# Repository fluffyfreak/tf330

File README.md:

# tf330

TF330 source files. 

Published under GPL v2. 

TF330 is distributed with absolutely no warranty. If you make a mistake you could blow up your CD32. I take no responsibility for this. 

The TF330 is an 030 accelerator fixed at 50Mhz with 64Mb of SDRAM (128Mb possible), WIFI support (via ESP8266) and is intended to work with CF cards or IDE2SD card type devices. The IDE interface does not work with long cables. It is intended to be CHEAP Because thats pretty much all Amiga users care about. 

**Before you start building :- You can buy these from Supaduper & AlenPPC (AmiBay) completely built for less than it will cost you to buy the parts and the time it will take you if you bill your time at minimum wage.**

If you have poor soldering skills and feel the need to mock me for not using through hole technology please dont bother. I've heard it all before and I will just laugh at you. Through hole sucks. 

Also do not ask me to reroute the board to a different DRC so you can use your local boardhouse. I dont feel like spending 100 hours of my time to save you $10. The DRC on this board is 7-7-7 and any boardhouse that doesnt totally suck can do this. Also it 4 layer and dont ask if i can be made 2 layer. The answer is no. 

If you need help with this the best place to get it is the exxos forum https://www.exxoshost.co.uk/forum/ 

Please do not message me directly. Start a thread. 

I do my best to help people who ask polite questions in public but if you make your inadequecies my problem then you are on your own. 

I dont care if you think my HDL is not pristine either. It works perfecly fine for what its intended to be. I lothe the wordy VHDL language.. it breaks the most basic principle of coding .. .DONT REPEAT YOURSELF. There is a full regression test suite in my development repo that I have chosen not to share.

The SDRAM Controller is derived from my Archie core and the clock controller code is designed to simulate a PLL with adjustable phase. 

This is not an exercise in German over engineering. Its properly engineered to do an exact task and nothing more. Its a simple repeatable board that works and there are about 500 of them built and working reliably.

I dont like forks because i dont like options. Options mean more testing and more testing = time. So if you fork you are on your own but if you fork and dont give credit I will make it my mission in life to punish you. I will summon the ancient retro spirits of evil like Jack Tramiel and have them haunt you for all time. You have been warned. 

I know this seems a bit hostile but really its just from hard experience of Amiga people. I give this out for free but there are people out there who will take the piss and try to rip off amiga users with clones baring their own name, others will get one of these off ebay for £15 and expect me to invest 100s of hours in helping them get it going. Yet others will try to be smart arses and tell me i've done X, Y or Z wrong and this will never work. If for any reason you decide this board does not measure up to whatever standard YOU think it should be... take a hike. I dont care. 

That said you are free to sell this on your webshop provided you give credit and do not vastly overprice it. However CE marking is your own issue not mine. 

On the other hand if you have an actual firmware bugfix send me a pull request with testing evidence. It will be appreciated greatly. 

For crashes please check that the crash doesnt happen in WinUAE for a CD32 with A1200 IDE and 64MB ZIII Ram before making a bug report. Most of the crashes we have seen over the years are repeatable in that environment. 

This version of the board is cloned from my private repository and is GPL. The version in my private repo is not GPL and anything derived from it is not subject to the GPL v2. It is highly likely that I will eventually release everything in my private repo. I just do so at a pace that keeps the freeloaders and price gougers from making much out of me.

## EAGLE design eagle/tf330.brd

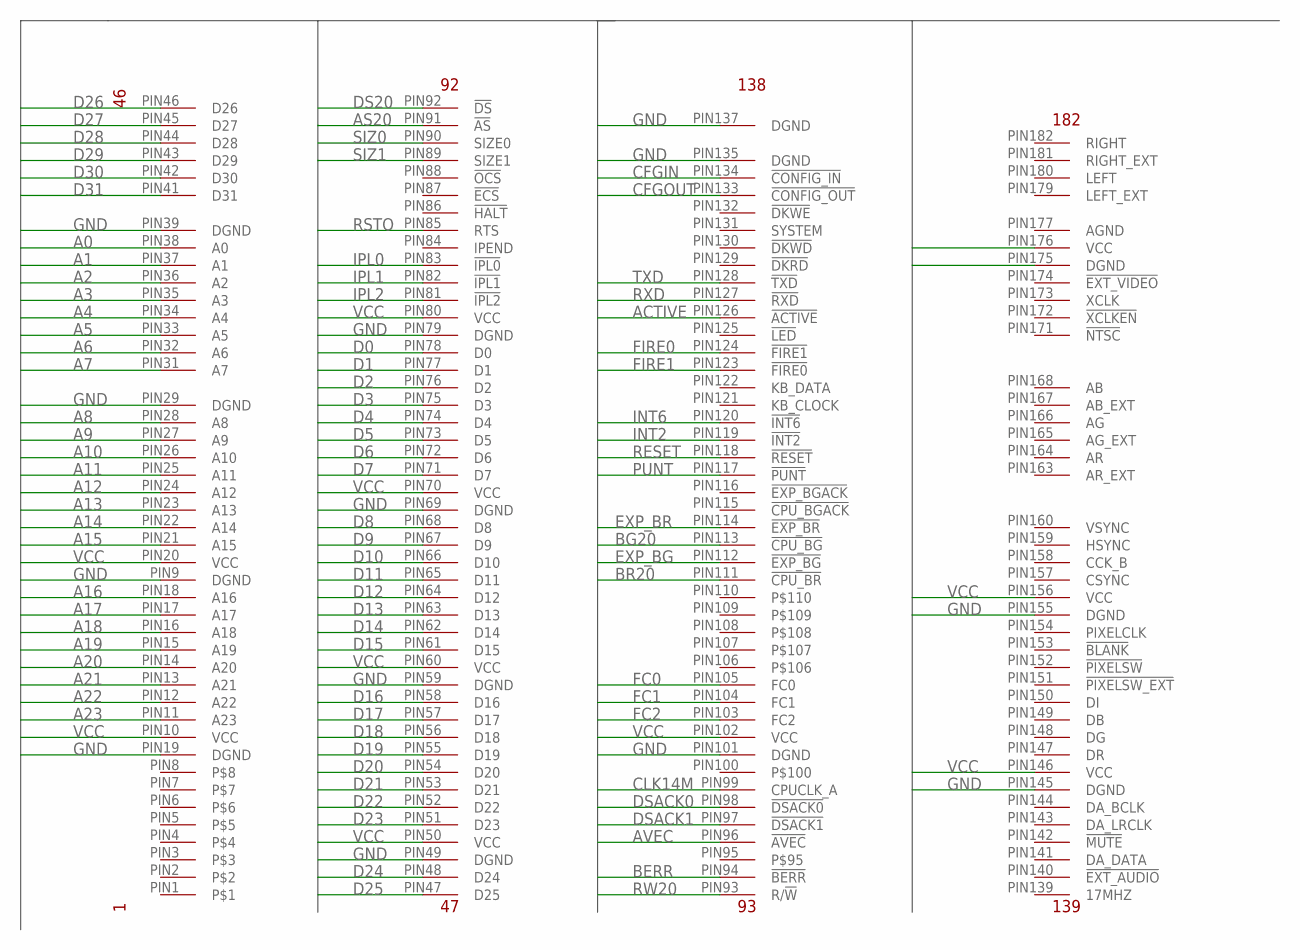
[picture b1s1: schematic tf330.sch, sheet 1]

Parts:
CONN1: MCA_CONN_182

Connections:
A0: CONN1.PIN38 (A0); also elsewhere on the board
A1: CONN1.PIN37 (A1); also elsewhere on the board
A2: CONN1.PIN36 (A2); also elsewhere on the board
A3: CONN1.PIN35 (A3); also elsewhere on the board
A4: CONN1.PIN34 (A4); also elsewhere on the board
A5: CONN1.PIN33 (A5); also elsewhere on the board
A6: CONN1.PIN32 (A6); also elsewhere on the board
A7: CONN1.PIN31 (A7); also elsewhere on the board
A8: CONN1.PIN28 (A8); also elsewhere on the board
A9: CONN1.PIN27 (A9); also elsewhere on the board
A10: CONN1.PIN26 (A10); also elsewhere on the board
A11: CONN1.PIN25 (A11); also elsewhere on the board
A12: CONN1.PIN24 (A12); also elsewhere on the board
A13: CONN1.PIN23 (A13); also elsewhere on the board
A14: CONN1.PIN22 (A14); also elsewhere on the board
A15: CONN1.PIN21 (A15); also elsewhere on the board
A16: CONN1.PIN18 (A16); also elsewhere on the board
A17: CONN1.PIN17 (A17); also elsewhere on the board
A18: CONN1.PIN16 (A18); also elsewhere on the board
A19: CONN1.PIN15 (A19); also elsewhere on the board
A20: CONN1.PIN14 (A20); also elsewhere on the board
A21: CONN1.PIN13 (A21); also elsewhere on the board
A22: CONN1.PIN12 (A22); also elsewhere on the board
A23: CONN1.PIN11 (A23); also elsewhere on the board
ACTIVE: CONN1.PIN126 (!ACTIVE); also elsewhere on the board
AGND: CONN1.PIN177 (AGND)
AS20: CONN1.PIN91 (!AS); also elsewhere on the board
AVEC: CONN1.PIN96 (!AVEC); also elsewhere on the board
BERR: CONN1.PIN94 (!BERR); also elsewhere on the board
BG20: CONN1.PIN113 (!CPU_BG); also elsewhere on the board
BR20: CONN1.PIN111 (!CPU_BR); also elsewhere on the board
CFGIN: CONN1.PIN134 (!CONFIG_IN)
CFGOUT: CONN1.PIN133 (!CONFIG_OUT)
CLK14M: CONN1.PIN99 (CPUCLK_A); also elsewhere on the board
D0: CONN1.PIN78 (D0); also elsewhere on the board
D1: CONN1.PIN77 (D1); also elsewhere on the board
D2: CONN1.PIN76 (D2); also elsewhere on the board
D3: CONN1.PIN75 (D3); also elsewhere on the board
D4: CONN1.PIN74 (D4); also elsewhere on the board
D5: CONN1.PIN73 (D5); also elsewhere on the board
D6: CONN1.PIN72 (D6); also elsewhere on the board
D7: CONN1.PIN71 (D7); also elsewhere on the board
D8: CONN1.PIN68 (D8); also elsewhere on the board
D9: CONN1.PIN67 (D9); also elsewhere on the board
D10: CONN1.PIN66 (D10); also elsewhere on the board
D11: CONN1.PIN65 (D11); also elsewhere on the board
D12: CONN1.PIN64 (D12); also elsewhere on the board
D13: CONN1.PIN63 (D13); also elsewhere on the board
D14: CONN1.PIN62 (D14); also elsewhere on the board
D15: CONN1.PIN61 (D15); also elsewhere on the board
D16: CONN1.PIN58 (D16); also elsewhere on the board
D17: CONN1.PIN57 (D17); also elsewhere on the board
D18: CONN1.PIN56 (D18); also elsewhere on the board
D19: CONN1.PIN55 (D19); also elsewhere on the board
D20: CONN1.PIN54 (D20); also elsewhere on the board
D21: CONN1.PIN53 (D21); also elsewhere on the board
D22: CONN1.PIN52 (D22); also elsewhere on the board
D23: CONN1.PIN51 (D23); also elsewhere on the board
D24: CONN1.PIN48 (D24); also elsewhere on the board
D25: CONN1.PIN47 (D25); also elsewhere on the board
D26: CONN1.PIN46 (D26); also elsewhere on the board
D27: CONN1.PIN45 (D27); also elsewhere on the board
D28: CONN1.PIN44 (D28); also elsewhere on the board
D29: CONN1.PIN43 (D29); also elsewhere on the board
D30: CONN1.PIN42 (D30); also elsewhere on the board
D31: CONN1.PIN41 (D31); also elsewhere on the board
DS20: CONN1.PIN92 (!DS); also elsewhere on the board
DSACK0: CONN1.PIN98 (!DSACK0); also elsewhere on the board
DSACK1: CONN1.PIN97 (!DSACK1); also elsewhere on the board
EXP_BG: CONN1.PIN112 (!EXP_BG); also elsewhere on the board
EXP_BR: CONN1.PIN114 (!EXP_BR); also elsewhere on the board
FC0: CONN1.PIN105 (FC0); also elsewhere on the board
FC1: CONN1.PIN104 (FC1); also elsewhere on the board
FC2: CONN1.PIN103 (FC2); also elsewhere on the board
FIRE0: CONN1.PIN124 (!FIRE1)
FIRE1: CONN1.PIN123 (!FIRE0)
GND: CONN1.PIN9 (DGND), CONN1.PIN19 (DGND), CONN1.PIN29 (DGND), CONN1.PIN39 (DGND), CONN1.PIN49 (DGND), CONN1.PIN59 (DGND), CONN1.PIN69 (DGND), CONN1.PIN79 (DGND), CONN1.PIN101 (DGND), CONN1.PIN135 (DGND), CONN1.PIN137 (DGND), CONN1.PIN145 (DGND), CONN1.PIN155 (DGND), CONN1.PIN175 (DGND); also elsewhere on the board
INT2: CONN1.PIN119 (!INT2); also elsewhere on the board
INT6: CONN1.PIN120 (!INT6)
IPL0: CONN1.PIN83 (!IPL0); also elsewhere on the board
IPL1: CONN1.PIN82 (!IPL1); also elsewhere on the board
IPL2: CONN1.PIN81 (!IPL2); also elsewhere on the board
PUNT: CONN1.PIN117 (!PUNT); also elsewhere on the board
RESET: CONN1.PIN118 (!RESET); also elsewhere on the board
RSTO: CONN1.PIN85 (RTS); also elsewhere on the board
RW20: CONN1.PIN93 (R/!W); also elsewhere on the board
RXD: CONN1.PIN127 (!RXD); also elsewhere on the board
SIZ0: CONN1.PIN90 (SIZE0); also elsewhere on the board
SIZ1: CONN1.PIN89 (SIZE1); also elsewhere on the board
TXD: CONN1.PIN128 (!TXD); also elsewhere on the board
VCC: CONN1.PIN10 (VCC), CONN1.PIN20 (VCC), CONN1.PIN50 (VCC), CONN1.PIN60 (VCC), CONN1.PIN70 (VCC), CONN1.PIN80 (VCC), CONN1.PIN102 (VCC), CONN1.PIN146 (VCC), CONN1.PIN156 (VCC), CONN1.PIN176 (VCC); also elsewhere on the board

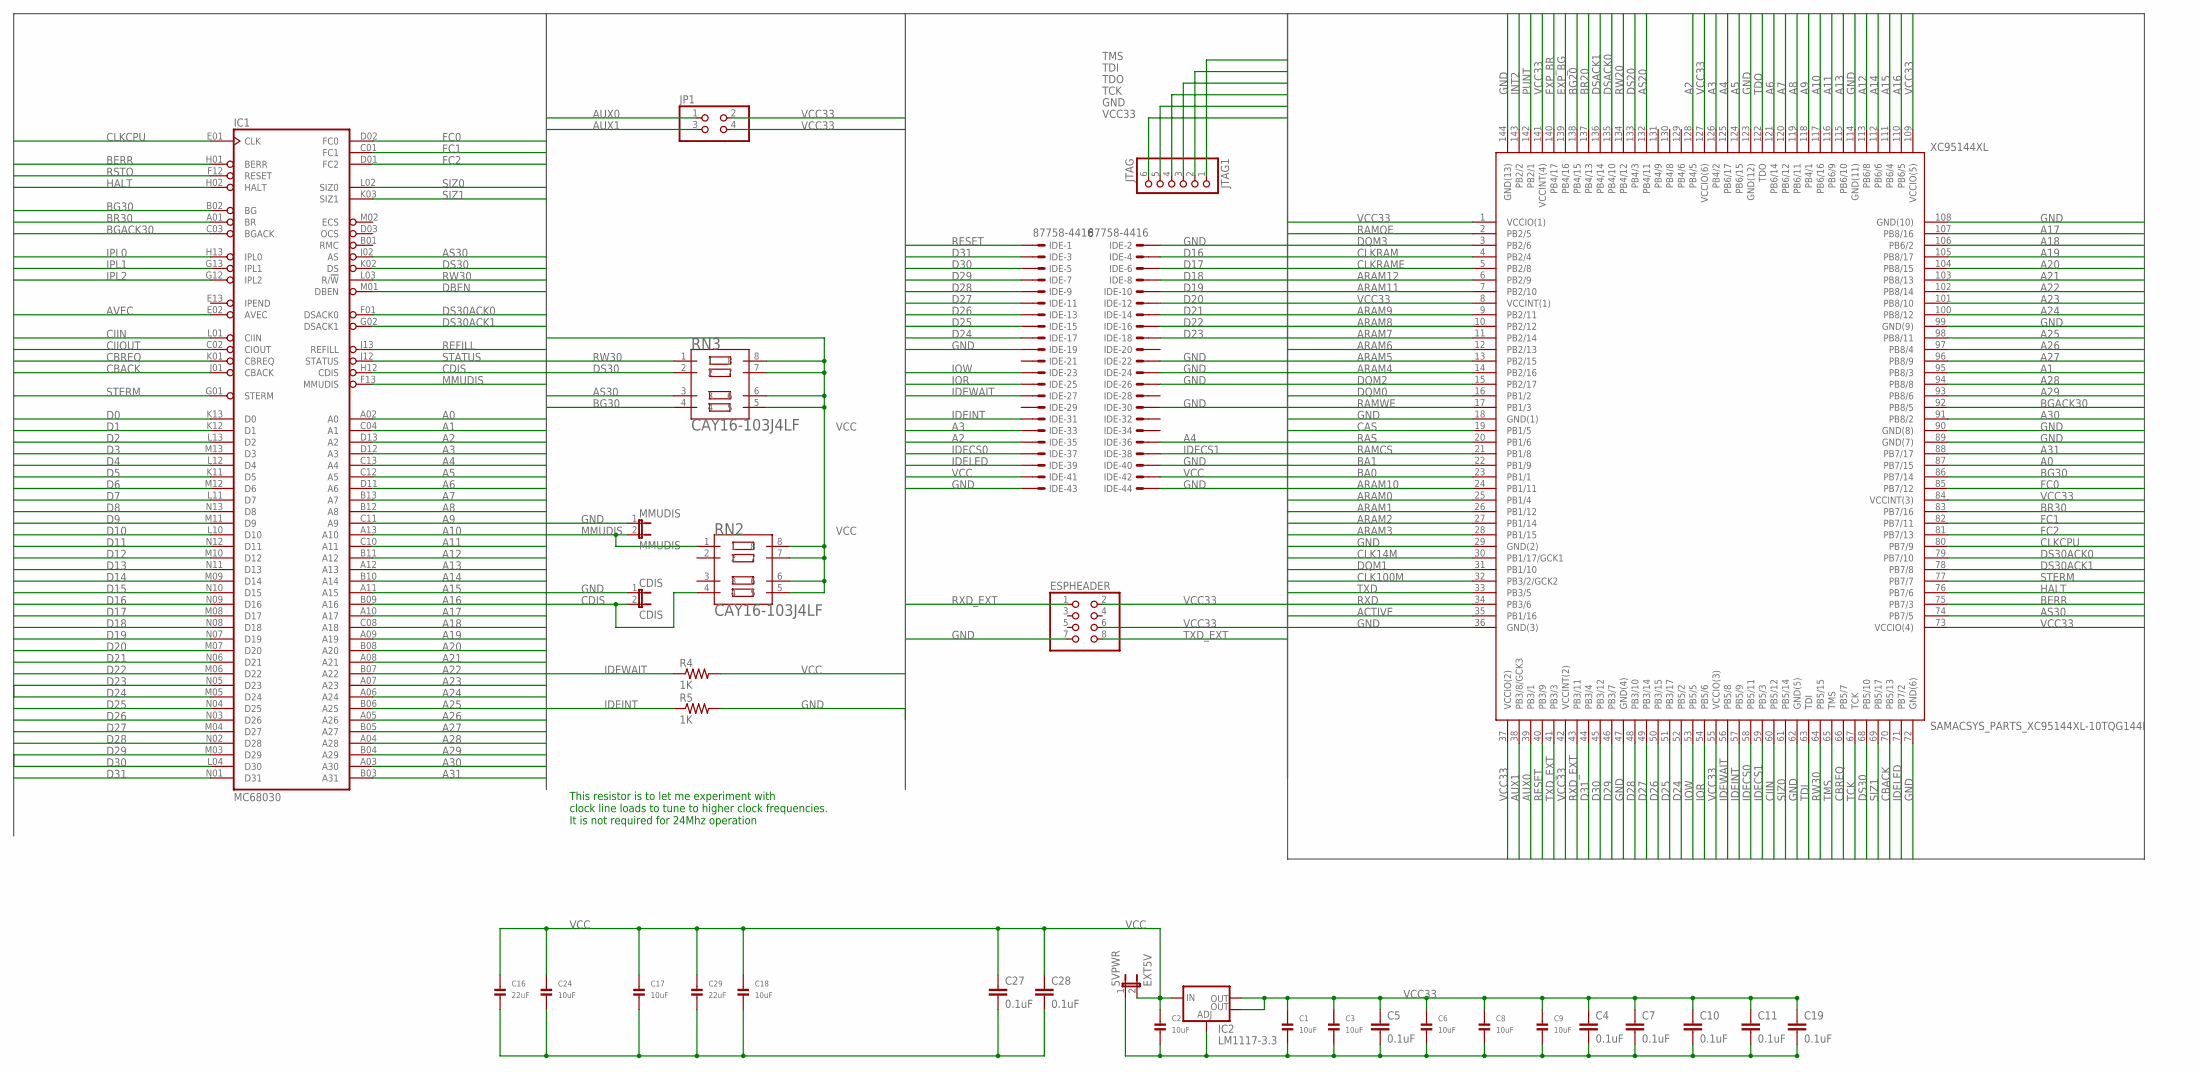
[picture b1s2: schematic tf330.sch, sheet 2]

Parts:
5VPWR: EXT5V; 1X02
C1, C2, C3, C6, C8, C9, C17, C18, C24: 10uF; 1206
C4, C5, C7, C10, C11, C19, C27, C28: 0.1uF; 0603-CAP
C16, C29: 22uF; 1206
CDIS: CDIS; 1X02
ESPHEADER: PINHD-2X4; 2X04
IC1: MC68030; MPGA128
IC2: LM1117-3.3; SOT223
IDE: 87758-4416
JP1: PINHD-2X2; 2X02
JTAG1: JTAG; 1X06_ROUND
MMUDIS: MMUDIS; 1X02
R4, R5: 1K; 0603
RN2, RN3: CAY16-103J4LF; RESCAXE80P320X160-8N
XC95144XL: SAMACSYS_PARTS_XC95144XL-10TQG144I; SAMACSYS_PARTS_QFP50P2200X2200X160-144N

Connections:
A0: IC1.A02 (A0), XC95144XL.87 (PB7/15); also elsewhere on the board
A1: IC1.C04 (A1), XC95144XL.95 (PB8/3); also elsewhere on the board
A2: IC1.D13 (A2), IDE.35, XC95144XL.128 (PB4/5); also elsewhere on the board
A3: IC1.D12 (A3), IDE.33, XC95144XL.126 (PB4/2); also elsewhere on the board
A4: IC1.C13 (A4), IDE.36, XC95144XL.125 (PB6/17); also elsewhere on the board
A5: IC1.C12 (A5), XC95144XL.124 (PB6/15); also elsewhere on the board
A6: IC1.D11 (A6), XC95144XL.121 (PB6/14); also elsewhere on the board
A7: IC1.B13 (A7), XC95144XL.120 (PB6/12); also elsewhere on the board
A8: IC1.B12 (A8), XC95144XL.119 (PB6/11); also elsewhere on the board
A9: IC1.C11 (A9), XC95144XL.118 (PB4/1); also elsewhere on the board
A10: IC1.A13 (A10), XC95144XL.117 (PB6/16); also elsewhere on the board
A11: IC1.C10 (A11), XC95144XL.116 (PB6/9); also elsewhere on the board
A12: IC1.B11 (A12), XC95144XL.113 (PB6/8); also elsewhere on the board
A13: IC1.A12 (A13), XC95144XL.115 (PB6/10); also elsewhere on the board
A14: IC1.B10 (A14), XC95144XL.112 (PB6/6); also elsewhere on the board
A15: IC1.A11 (A15), XC95144XL.111 (PB6/4); also elsewhere on the board
A16: IC1.B09 (A16), XC95144XL.110 (PB6/5); also elsewhere on the board
A17: IC1.A10 (A17), XC95144XL.107 (PB8/16); also elsewhere on the board
A18: IC1.C08 (A18), XC95144XL.106 (PB6/2); also elsewhere on the board
A19: IC1.A09 (A19), XC95144XL.105 (PB8/17); also elsewhere on the board
A20: IC1.B08 (A20), XC95144XL.104 (PB8/15); also elsewhere on the board
A21: IC1.A08 (A21), XC95144XL.103 (PB8/13); also elsewhere on the board
A22: IC1.B07 (A22), XC95144XL.102 (PB8/14); also elsewhere on the board
A23: IC1.A07 (A23), XC95144XL.101 (PB8/10); also elsewhere on the board
A24: IC1.A06 (A24), XC95144XL.100 (PB8/12)
A25: IC1.B06 (A25), XC95144XL.98 (PB8/11)
A26: IC1.A05 (A26), XC95144XL.97 (PB8/4)
A27: IC1.B05 (A27), XC95144XL.96 (PB8/9)
A28: IC1.A04 (A28), XC95144XL.94 (PB8/8)
A29: IC1.B04 (A29), XC95144XL.93 (PB8/6)
A30: IC1.A03 (A30), XC95144XL.91 (PB8/2)
A31: IC1.B03 (A31), XC95144XL.88 (PB7/17)
ACTIVE: XC95144XL.35 (PB1/16); also elsewhere on the board
ARAM0: XC95144XL.25 (PB1/4); also elsewhere on the board
ARAM1: XC95144XL.26 (PB1/12); also elsewhere on the board
ARAM2: XC95144XL.27 (PB1/14); also elsewhere on the board
ARAM3: XC95144XL.28 (PB1/15); also elsewhere on the board
ARAM4: XC95144XL.14 (PB2/16); also elsewhere on the board
ARAM5: XC95144XL.13 (PB2/15); also elsewhere on the board
ARAM6: XC95144XL.12 (PB2/13); also elsewhere on the board
ARAM7: XC95144XL.11 (PB2/14); also elsewhere on the board
ARAM8: XC95144XL.10 (PB2/12); also elsewhere on the board
ARAM9: XC95144XL.9 (PB2/11); also elsewhere on the board
ARAM10: XC95144XL.24 (PB1/11); also elsewhere on the board
ARAM11: XC95144XL.7 (PB2/10); also elsewhere on the board
ARAM12: XC95144XL.6 (PB2/9); also elsewhere on the board
AS20: XC95144XL.132 (PB4/11); also elsewhere on the board
AS30: IC1.J02 (AS), RN3.3, XC95144XL.74 (PB7/5)
AUX0: JP1.1, XC95144XL.39 (PB3/1)
AUX1: JP1.3, XC95144XL.38 (PB3/8/GCK3)
AVEC: IC1.E02 (AVEC); also elsewhere on the board
BA0: XC95144XL.23 (PB1/1); also elsewhere on the board
BA1: XC95144XL.22 (PB1/9); also elsewhere on the board
BERR: IC1.H01 (BERR), XC95144XL.75 (PB7/3); also elsewhere on the board
BG20: XC95144XL.138 (PB4/15); also elsewhere on the board
BG30: IC1.B02 (BG), RN3.4, XC95144XL.86 (PB7/14)
BGACK30: IC1.C03 (BGACK), XC95144XL.92 (PB8/5)
BR20: XC95144XL.137 (PB4/13); also elsewhere on the board
BR30: IC1.A01 (BR), XC95144XL.83 (PB7/16)
CAS: XC95144XL.19 (PB1/5); also elsewhere on the board
CBACK: IC1.J01 (CBACK), XC95144XL.70 (PB5/13)
CBREQ: IC1.K01 (CBREQ), XC95144XL.66 (PB5/7)
CDIS: CDIS.2, IC1.H12 (CDIS), RN2.4
CIIN: IC1.L01 (CIIN), XC95144XL.60 (PB5/12)
CIIOUT: IC1.C02 (CIOUT)
CLK14M: XC95144XL.30 (PB1/17/GCK1); also elsewhere on the board
CLK100M: XC95144XL.32 (PB3/2/GCK2); also elsewhere on the board
CLKCPU: IC1.E01 (CLK), XC95144XL.80 (PB7/9)
CLKRAM: XC95144XL.4 (PB2/4); also elsewhere on the board
CLKRAME: XC95144XL.5 (PB2/8); also elsewhere on the board
D0: IC1.K13 (D0); also elsewhere on the board
D1: IC1.K12 (D1); also elsewhere on the board
D2: IC1.L13 (D2); also elsewhere on the board
D3: IC1.M13 (D3); also elsewhere on the board
D4: IC1.L12 (D4); also elsewhere on the board
D5: IC1.K11 (D5); also elsewhere on the board
D6: IC1.M12 (D6); also elsewhere on the board
D7: IC1.L11 (D7); also elsewhere on the board
D8: IC1.N13 (D8); also elsewhere on the board
D9: IC1.M11 (D9); also elsewhere on the board
D10: IC1.L10 (D10); also elsewhere on the board
D11: IC1.N12 (D11); also elsewhere on the board
D12: IC1.M10 (D12); also elsewhere on the board
D13: IC1.N11 (D13); also elsewhere on the board
D14: IC1.M09 (D14); also elsewhere on the board
D15: IC1.N10 (D15); also elsewhere on the board
D16: IC1.N09 (D16), IDE.4; also elsewhere on the board
D17: IC1.M08 (D17), IDE.6; also elsewhere on the board
D18: IC1.N08 (D18), IDE.8; also elsewhere on the board
D19: IC1.N07 (D19), IDE.10; also elsewhere on the board
D20: IC1.M07 (D20), IDE.12; also elsewhere on the board
D21: IC1.N06 (D21), IDE.14; also elsewhere on the board
D22: IC1.M06 (D22), IDE.16; also elsewhere on the board
D23: IC1.N05 (D23), IDE.18; also elsewhere on the board
D24: IC1.M05 (D24), IDE.17, XC95144XL.52 (PB5/2); also elsewhere on the board
D25: IC1.N04 (D25), IDE.15, XC95144XL.51 (PB3/17); also elsewhere on the board
D26: IC1.N03 (D26), IDE.13, XC95144XL.50 (PB3/15); also elsewhere on the board
D27: IC1.M04 (D27), IDE.11, XC95144XL.49 (PB3/14); also elsewhere on the board
D28: IC1.N02 (D28), IDE.9, XC95144XL.48 (PB3/10); also elsewhere on the board
D29: IC1.M03 (D29), IDE.7, XC95144XL.46 (PB3/7); also elsewhere on the board
D30: IC1.L04 (D30), IDE.5, XC95144XL.45 (PB3/12); also elsewhere on the board
D31: IC1.N01 (D31), IDE.3, XC95144XL.44 (PB3/4); also elsewhere on the board
DBEN: IC1.M01 (DBEN)
DQM0: XC95144XL.16 (PB1/2); also elsewhere on the board
DQM1: XC95144XL.31 (PB1/10); also elsewhere on the board
DQM2: XC95144XL.15 (PB2/17); also elsewhere on the board
DQM3: XC95144XL.3 (PB2/6); also elsewhere on the board
DS20: XC95144XL.133 (PB4/3); also elsewhere on the board
DS30: IC1.K02 (DS), RN3.2, XC95144XL.68 (PB5/10)
DS30ACK0: IC1.F01 (DSACK0), XC95144XL.79 (PB7/10)
DS30ACK1: IC1.G02 (DSACK1), XC95144XL.78 (PB7/8)
DSACK0: XC95144XL.135 (PB4/10); also elsewhere on the board
DSACK1: XC95144XL.136 (PB4/14); also elsewhere on the board
EXP_BG: XC95144XL.139 (PB4/16); also elsewhere on the board
EXP_BR: XC95144XL.140 (PB4/17); also elsewhere on the board
FC0: IC1.D02 (FC0), XC95144XL.85 (PB7/12); also elsewhere on the board
FC1: IC1.C01 (FC1), XC95144XL.82 (PB7/11); also elsewhere on the board
FC2: IC1.D01 (FC2), XC95144XL.81 (PB7/13); also elsewhere on the board
GND: 5VPWR.1, C1.2, C2.2, C3.2, C4.2, C5.2, C6.2, C7.2, C8.2, C9.2, C10.2, C11.2, C16.2, C17.2, C18.2, C19.2, C24.2, C27.2, C28.2, C29.2, CDIS.1, ESPHEADER.7, IC1.C05 (GND), IC1.C07 (GND), IC1.C09 (GND), IC1.E03 (GND), IC1.E11 (GND), IC1.F03 (GND), IC1.G03 (GND), IC1.G11 (GND), IC1.J03 (GND), IC1.J11 (GND), IC1.L05 (GND), IC1.L07 (GND), IC1.L08 (GND), IC1.L09 (GND), IC2.1 (ADJ), IDE.2, IDE.19, IDE.22, IDE.24, IDE.26, IDE.30, IDE.40, IDE.43, IDE.44, JTAG1.5, MMUDIS.1, R5.2, XC95144XL.18 (GND(1)), XC95144XL.29 (GND(2)), XC95144XL.36 (GND(3)), XC95144XL.47 (GND(4)), XC95144XL.62 (GND(5)), XC95144XL.72 (GND(6)), XC95144XL.89 (GND(7)), XC95144XL.90 (GND(8)), XC95144XL.99 (GND(9)), XC95144XL.108 (GND(10)), XC95144XL.114 (GND(11)), XC95144XL.123 (GND(12)), XC95144XL.144 (GND(13)); also elsewhere on the board
HALT: IC1.H02 (HALT), XC95144XL.76 (PB7/6)
IDECS0: IDE.37, XC95144XL.58 (PB5/11)
IDECS1: IDE.38, XC95144XL.59 (PB5/3)
IDEINT: IDE.31, R5.1, XC95144XL.57 (PB5/9)
IDELED: IDE.39, XC95144XL.71 (PB7/2)
IDEWAIT: IDE.27, R4.1, XC95144XL.56 (PB5/8)
INT2: XC95144XL.143 (PB2/2); also elsewhere on the board
IOR: IDE.25, XC95144XL.54 (PB5/6)
IOW: IDE.23, XC95144XL.53 (PB5/5)
IPL0: IC1.H13 (IPL0); also elsewhere on the board
IPL1: IC1.G13 (IPL1); also elsewhere on the board
IPL2: IC1.G12 (IPL2); also elsewhere on the board
MMUDIS: IC1.F13 (MMUDIS), MMUDIS.2, RN2.1
PUNT: XC95144XL.142 (PB2/1); also elsewhere on the board
RAMCS: XC95144XL.21 (PB1/8); also elsewhere on the board
RAMOE: XC95144XL.2 (PB2/5); also elsewhere on the board
RAMWE: XC95144XL.17 (PB1/3); also elsewhere on the board
RAS: XC95144XL.20 (PB1/6); also elsewhere on the board
REFILL: IC1.J13 (REFILL)
RESET: IDE.1, XC95144XL.40 (PB3/9); also elsewhere on the board
RSTO: IC1.F12 (RESET); also elsewhere on the board
RW20: XC95144XL.134 (PB4/12); also elsewhere on the board
RW30: IC1.L03 (R/!W), RN3.1, XC95144XL.64 (PB5/15)
RXD: XC95144XL.34 (PB3/6); also elsewhere on the board
RXD_EXT: ESPHEADER.1, XC95144XL.43 (PB3/11)
SIZ0: IC1.L02 (SIZ0), XC95144XL.61 (PB5/14); also elsewhere on the board
SIZ1: IC1.K03 (SIZ1), XC95144XL.69 (PB5/17); also elsewhere on the board
STATUS: IC1.J12 (STATUS)
STERM: IC1.G01 (STERM), XC95144XL.77 (PB7/7)
TCK: JTAG1.4, XC95144XL.67 (TCK)
TDI: JTAG1.2, XC95144XL.63 (TDI)
TDO: JTAG1.3, XC95144XL.122 (TDO)
TMS: JTAG1.1, XC95144XL.65 (TMS)
TXD: XC95144XL.33 (PB3/5); also elsewhere on the board
TXD_EXT: ESPHEADER.8, XC95144XL.41 (PB3/3)
VCC: 5VPWR.2, C2.1, C16.1, C17.1, C18.1, C24.1, C27.1, C28.1, C29.1, IC1.C06 (VCC), IC1.D04 (VCC), IC1.D10 (VCC), IC1.F02 (VCC), IC1.F11 (VCC), IC1.H03 (VCC), IC1.H11 (VCC), IC1.K04 (VCC), IC1.K10 (VCC), IC1.L06 (VCC), IC2.3 (IN), IDE.41, IDE.42, R4.2, RN2.5, RN2.6, RN2.7, RN2.8, RN3.5, RN3.6, RN3.7, RN3.8; also elsewhere on the board
VCC33: C1.1, C3.1, C4.1, C5.1, C6.1, C7.1, C8.1, C9.1, C10.1, C11.1, C19.1, ESPHEADER.2, ESPHEADER.6, IC2.2 (OUT), IC2.4 (OUT), JP1.2, JP1.4, JTAG1.6, XC95144XL.1 (VCCIO(1)), XC95144XL.8 (VCCINT(1)), XC95144XL.37 (VCCIO(2)), XC95144XL.42 (VCCINT(2)), XC95144XL.55 (VCCIO(3)), XC95144XL.73 (VCCIO(4)), XC95144XL.84 (VCCINT(3)), XC95144XL.109 (VCCIO(5)), XC95144XL.127 (VCCIO(6)), XC95144XL.141 (VCCINT(4)); also elsewhere on the board

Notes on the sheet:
This resistor is to let me experiment with clock line loads to tune to higher clock frequencies. It is not required for 24Mhz operation

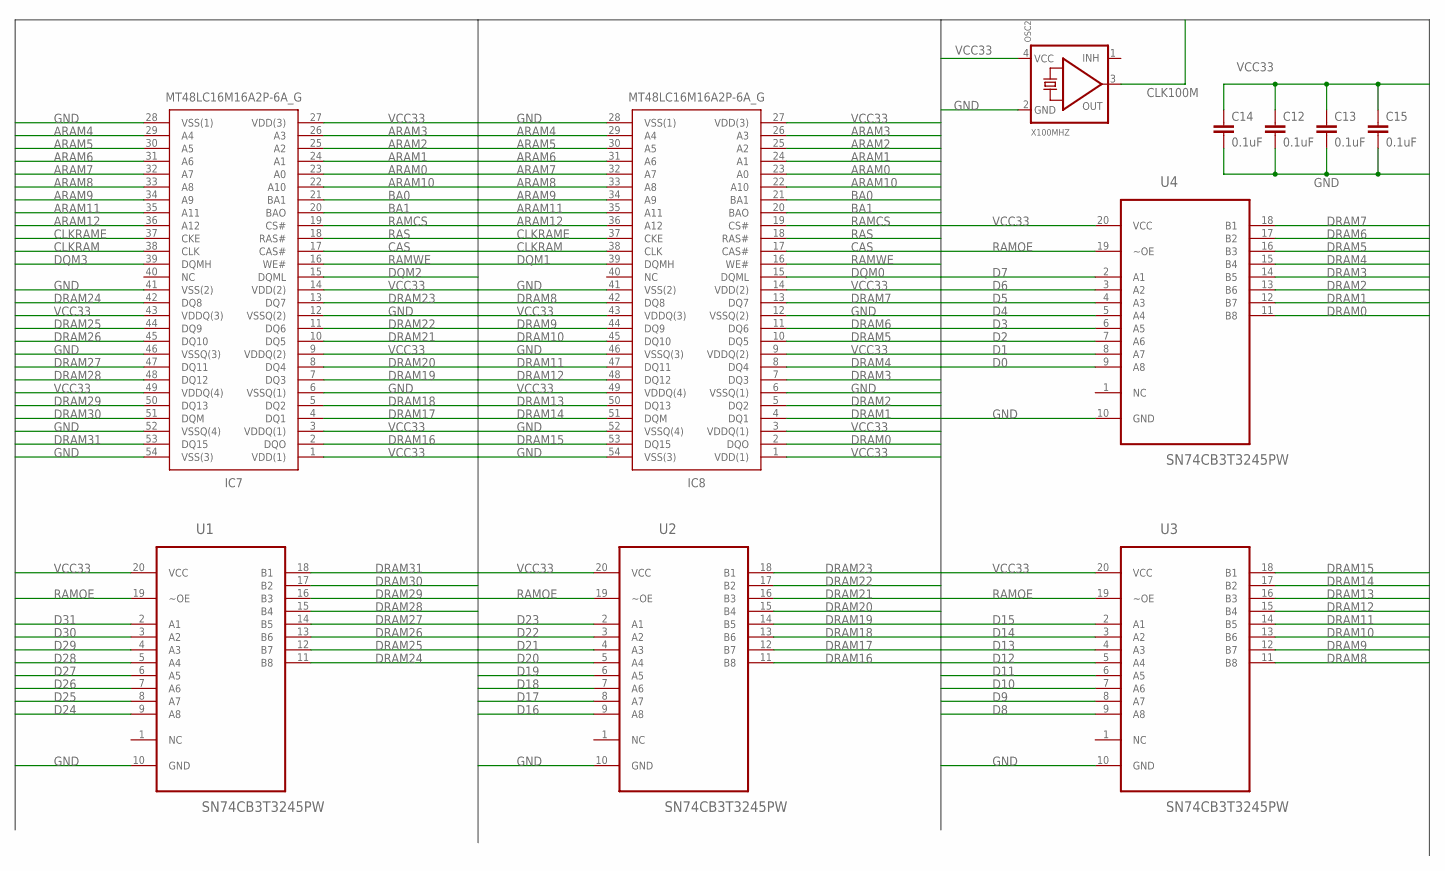
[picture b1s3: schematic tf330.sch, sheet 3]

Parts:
C12, C13, C14, C15: 0.1uF; 0603-CAP
IC7, IC8: MT48LC16M16A2P-6A_G; SOP80P1176X120-54N
OSC2: X100MHZ; OSC_7X5MM
U1, U2, U3, U4: SN74CB3T3245PW; SOP65P640X120-20N

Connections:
ARAM0: IC7.23 (A0), IC8.23 (A0); also elsewhere on the board
ARAM1: IC7.24 (A1), IC8.24 (A1); also elsewhere on the board
ARAM2: IC7.25 (A2), IC8.25 (A2); also elsewhere on the board
ARAM3: IC7.26 (A3), IC8.26 (A3); also elsewhere on the board
ARAM4: IC7.29 (A4), IC8.29 (A4); also elsewhere on the board
ARAM5: IC7.30 (A5), IC8.30 (A5); also elsewhere on the board
ARAM6: IC7.31 (A6), IC8.31 (A6); also elsewhere on the board
ARAM7: IC7.32 (A7), IC8.32 (A7); also elsewhere on the board
ARAM8: IC7.33 (A8), IC8.33 (A8); also elsewhere on the board
ARAM9: IC7.34 (A9), IC8.34 (A9); also elsewhere on the board
ARAM10: IC7.22 (A10), IC8.22 (A10); also elsewhere on the board
ARAM11: IC7.35 (A11), IC8.35 (A11); also elsewhere on the board
ARAM12: IC7.36 (A12), IC8.36 (A12); also elsewhere on the board
BA0: IC7.21 (BA1), IC8.21 (BA1); also elsewhere on the board
BA1: IC7.20 (BAO), IC8.20 (BAO); also elsewhere on the board
CAS: IC7.17 (CAS#), IC8.17 (CAS#); also elsewhere on the board
CLK100M: OSC2.3 (OUT); also elsewhere on the board
CLKRAM: IC7.38 (CLK), IC8.38 (CLK); also elsewhere on the board
CLKRAME: IC7.37 (CKE), IC8.37 (CKE); also elsewhere on the board
D0: U4.9 (A8); also elsewhere on the board
D1: U4.8 (A7); also elsewhere on the board
D2: U4.7 (A6); also elsewhere on the board
D3: U4.6 (A5); also elsewhere on the board
D4: U4.5 (A4); also elsewhere on the board
D5: U4.4 (A3); also elsewhere on the board
D6: U4.3 (A2); also elsewhere on the board
D7: U4.2 (A1); also elsewhere on the board
D8: U3.9 (A8); also elsewhere on the board
D9: U3.8 (A7); also elsewhere on the board
D10: U3.7 (A6); also elsewhere on the board
D11: U3.6 (A5); also elsewhere on the board
D12: U3.5 (A4); also elsewhere on the board
D13: U3.4 (A3); also elsewhere on the board
D14: U3.3 (A2); also elsewhere on the board
D15: U3.2 (A1); also elsewhere on the board
D16: U2.9 (A8); also elsewhere on the board
D17: U2.8 (A7); also elsewhere on the board
D18: U2.7 (A6); also elsewhere on the board
D19: U2.6 (A5); also elsewhere on the board
D20: U2.5 (A4); also elsewhere on the board
D21: U2.4 (A3); also elsewhere on the board
D22: U2.3 (A2); also elsewhere on the board
D23: U2.2 (A1); also elsewhere on the board
D24: U1.9 (A8); also elsewhere on the board
D25: U1.8 (A7); also elsewhere on the board
D26: U1.7 (A6); also elsewhere on the board
D27: U1.6 (A5); also elsewhere on the board
D28: U1.5 (A4); also elsewhere on the board
D29: U1.4 (A3); also elsewhere on the board
D30: U1.3 (A2); also elsewhere on the board
D31: U1.2 (A1); also elsewhere on the board
DQM0: IC8.15 (DQML); also elsewhere on the board
DQM1: IC8.39 (DQMH); also elsewhere on the board
DQM2: IC7.15 (DQML); also elsewhere on the board
DQM3: IC7.39 (DQMH); also elsewhere on the board
DRAM0: IC8.2 (DQO), U4.11 (B8)
DRAM1: IC8.4 (DQ1), U4.12 (B7)
DRAM2: IC8.5 (DQ2), U4.13 (B6)
DRAM3: IC8.7 (DQ3), U4.14 (B5)
DRAM4: IC8.8 (DQ4), U4.15 (B4)
DRAM5: IC8.10 (DQ5), U4.16 (B3)
DRAM6: IC8.11 (DQ6), U4.17 (B2)
DRAM7: IC8.13 (DQ7), U4.18 (B1)
DRAM8: IC8.42 (DQ8), U3.11 (B8)
DRAM9: IC8.44 (DQ9), U3.12 (B7)
DRAM10: IC8.45 (DQ10), U3.13 (B6)
DRAM11: IC8.47 (DQ11), U3.14 (B5)
DRAM12: IC8.48 (DQ12), U3.15 (B4)
DRAM13: IC8.50 (DQ13), U3.16 (B3)
DRAM14: IC8.51 (DQM), U3.17 (B2)
DRAM15: IC8.53 (DQ15), U3.18 (B1)
DRAM16: IC7.2 (DQO), U2.11 (B8)
DRAM17: IC7.4 (DQ1), U2.12 (B7)
DRAM18: IC7.5 (DQ2), U2.13 (B6)
DRAM19: IC7.7 (DQ3), U2.14 (B5)
DRAM20: IC7.8 (DQ4), U2.15 (B4)
DRAM21: IC7.10 (DQ5), U2.16 (B3)
DRAM22: IC7.11 (DQ6), U2.17 (B2)
DRAM23: IC7.13 (DQ7), U2.18 (B1)
DRAM24: IC7.42 (DQ8), U1.11 (B8)
DRAM25: IC7.44 (DQ9), U1.12 (B7)
DRAM26: IC7.45 (DQ10), U1.13 (B6)
DRAM27: IC7.47 (DQ11), U1.14 (B5)
DRAM28: IC7.48 (DQ12), U1.15 (B4)
DRAM29: IC7.50 (DQ13), U1.16 (B3)
DRAM30: IC7.51 (DQM), U1.17 (B2)
DRAM31: IC7.53 (DQ15), U1.18 (B1)
GND: C12.2, C13.2, C14.2, C15.2, IC7.6 (VSSQ(1)), IC7.12 (VSSQ(2)), IC7.28 (VSS(1)), IC7.41 (VSS(2)), IC7.46 (VSSQ(3)), IC7.52 (VSSQ(4)), IC7.54 (VSS(3)), IC8.6 (VSSQ(1)), IC8.12 (VSSQ(2)), IC8.28 (VSS(1)), IC8.41 (VSS(2)), IC8.46 (VSSQ(3)), IC8.52 (VSSQ(4)), IC8.54 (VSS(3)), OSC2.2 (GND), U1.10 (GND), U2.10 (GND), U3.10 (GND), U4.10 (GND); also elsewhere on the board
RAMCS: IC7.19 (CS#), IC8.19 (CS#); also elsewhere on the board
RAMOE: U1.19 (~OE), U2.19 (~OE), U3.19 (~OE), U4.19 (~OE); also elsewhere on the board
RAMWE: IC7.16 (WE#), IC8.16 (WE#); also elsewhere on the board
RAS: IC7.18 (RAS#), IC8.18 (RAS#); also elsewhere on the board
VCC33: C12.1, C13.1, C14.1, C15.1, IC7.1 (VDD(1)), IC7.3 (VDDQ(1)), IC7.9 (VDDQ(2)), IC7.14 (VDD(2)), IC7.27 (VDD(3)), IC7.43 (VDDQ(3)), IC7.49 (VDDQ(4)), IC8.1 (VDD(1)), IC8.3 (VDDQ(1)), IC8.9 (VDDQ(2)), IC8.14 (VDD(2)), IC8.27 (VDD(3)), IC8.43 (VDDQ(3)), IC8.49 (VDDQ(4)), OSC2.4 (VCC), U1.20 (VCC), U2.20 (VCC), U3.20 (VCC), U4.20 (VCC); also elsewhere on the board

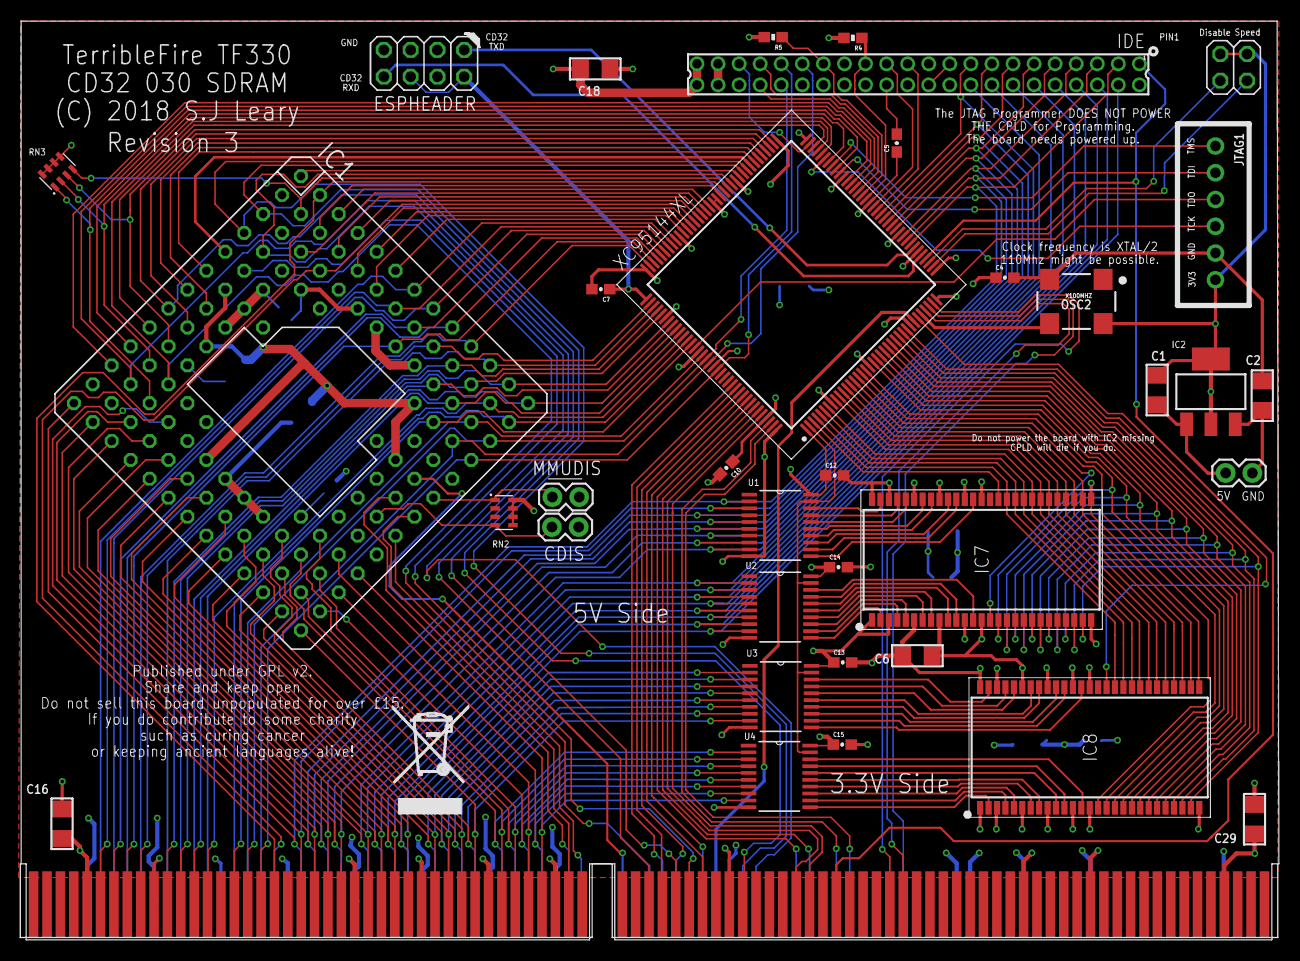
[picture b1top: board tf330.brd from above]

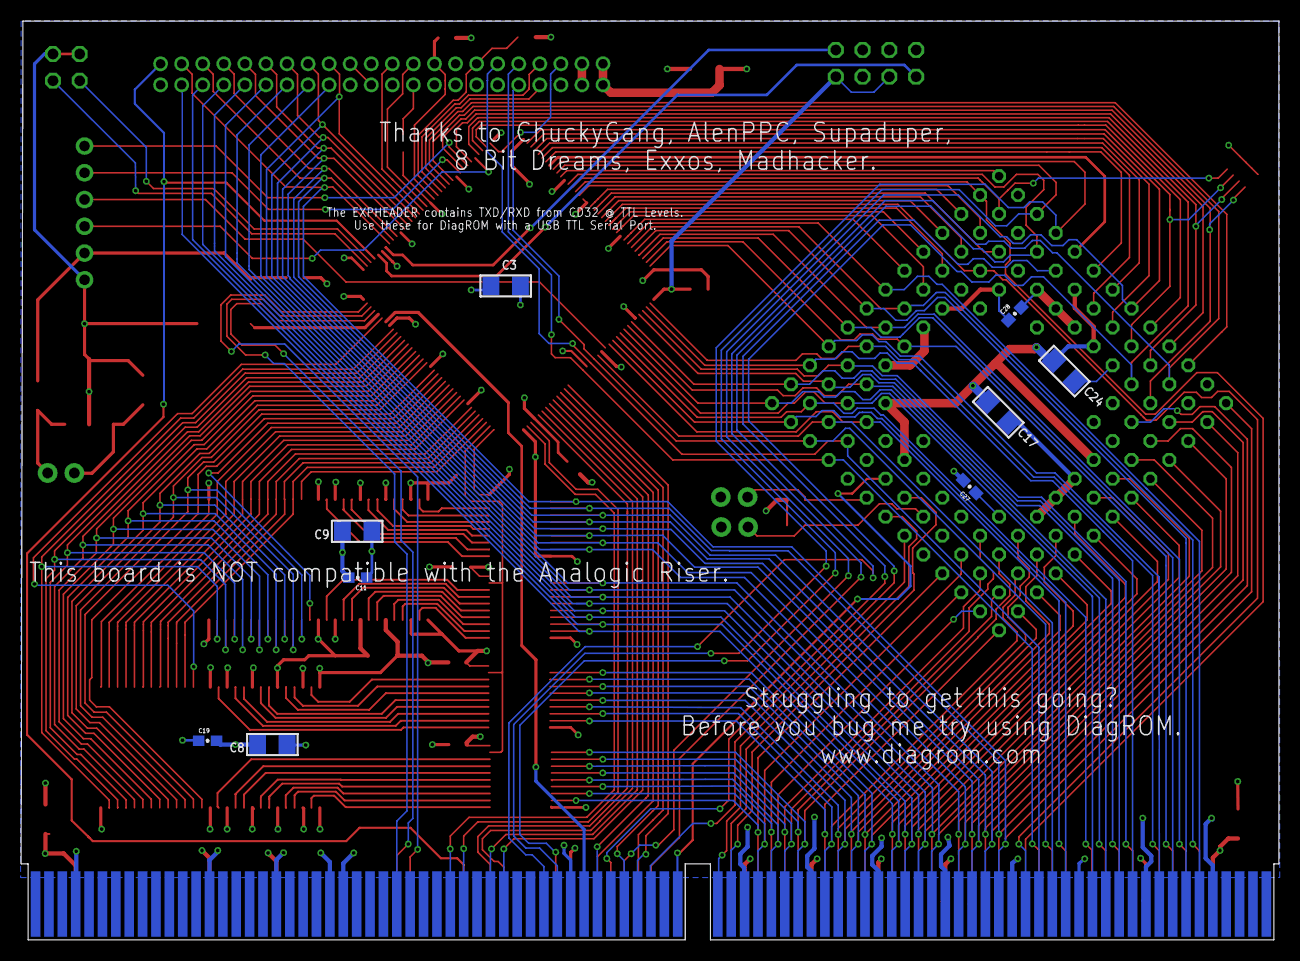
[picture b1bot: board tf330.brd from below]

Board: 4 copper layers, 119.4 x 87.2 mm, 45 parts (9 on the bottom side), 184 nets.

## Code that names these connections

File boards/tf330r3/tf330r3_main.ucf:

# Copyright (C) 2016-2017, Stephen J. Leary
# All rights reserved.
#
# This file is part of TF530 (Terrible Fire 030 Accelerator)
#
# TF530 is free software: you can redistribute it and/or modify
# it under the terms of the GNU General Public License as published by
# the Free Software Foundation, either version 3 of the License, or
# (at your option) any later version.
#
# TF530 is distributed in the hope that it will be useful,
# but WITHOUT ANY WARRANTY; without even the implied warranty of
# MERCHANTABILITY or FITNESS FOR A PARTICULAR PURPOSE.  See the
# GNU General Public License for more details.
#
# You should have received a copy of the GNU General Public License
# along with TF330. If not, see <http://www.gnu.org/licenses/>.

#Clocks
NET "CLK100M"		LOC="32";
NET "CLK100M" BUFG=CLK;
NET "CLK100M" TNM_NET = "CLK100M"; # gives the net clk a group name as CLK100M

NET "CLK14M"		LOC="30";
NET "CLK14M" BUFG=CLK;
NET "CLK14M" TNM_NET = "CLK14M"; # gives the net clk a group name as CLK14M

NET "A<0>"      LOC="87";
NET "A<1>"      LOC="95";
NET "A<2>"      LOC="128";
NET "A<3>"      LOC="126";
NET "A<4>"      LOC="125";
NET "A<5>"      LOC="124";
NET "A<6>"      LOC="121";
NET "A<7>"      LOC="120";
NET "A<8>"      LOC="119";
NET "A<9>"      LOC="118";
NET "A<10>"      LOC="117";
NET "A<11>"      LOC="116";
NET "A<12>"      LOC="113";
NET "A<13>"      LOC="115";
NET "A<14>"      LOC="112";
NET "A<15>"      LOC="111";
NET "A<16>"      LOC="110";
NET "A<17>"      LOC="107";
NET "A<18>"      LOC="106";
NET "A<19>"      LOC="105";
NET "A<20>"      LOC="104";
NET "A<21>"      LOC="103";
NET "A<22>"      LOC="102";
NET "A<23>"      LOC="101";
NET "A<24>"      LOC="100";
NET "A<25>"      LOC="98";
NET "A<26>"      LOC="97";
NET "A<27>"      LOC="96";
NET "A<28>"      LOC="94";
NET "A<29>"      LOC="93";
NET "A<30>"      LOC="91";
NET "A<31>"      LOC="88";
NET "ACTIVE"      LOC="35";
NET "ARAM<0>"      LOC="25";
NET "ARAM<1>"      LOC="26";
NET "ARAM<2>"      LOC="27";
NET "ARAM<3>"      LOC="28";
NET "ARAM<4>"      LOC="14";
NET "ARAM<5>"      LOC="13";
NET "ARAM<6>"      LOC="12";
NET "ARAM<7>"      LOC="11";
NET "ARAM<8>"      LOC="10";
NET "ARAM<9>"      LOC="9";
NET "ARAM<10>"      LOC="24";
NET "ARAM<11>"      LOC="7";
NET "ARAM<12>"      LOC="6";
NET "AS20"      LOC="132";
NET "AS30"      LOC="74";
NET "DISABLE"      LOC="39";
NET AUXGND      LOC="38";
#NET "AUX<2>"      LOC="40";
NET "BA<0>"      LOC="23";
NET "BA<1>"      LOC="22";
NET "BERR"      LOC="75";
NET "BG20"      LOC="138";
NET "BG30"      LOC="86";
NET "BGACK30"      LOC="92";
NET "BR20"      LOC="137";
NET "BR30"      LOC="83";
NET "CAS"      LOC="19";
NET "CBACK"      LOC="70";
NET "CBREQ"      LOC="66";
NET "CIIN"      LOC="60";
NET "CLKCPU"      LOC="80";
NET "CLKRAM"      LOC="4";
NET "CLKRAME"      LOC="5";
NET "D<24>"      LOC="52";
NET "D<25>"      LOC="51";
NET "D<26>"      LOC="50";
NET "D<27>"      LOC="49";
NET "D<28>"      LOC="48";
NET "D<29>"      LOC="46";
NET "D<30>"      LOC="45";
NET "D<31>"      LOC="44";
NET "DQM<0>"      LOC="16";
NET "DQM<1>"      LOC="31";
NET "DQM<2>"      LOC="15";
NET "DQM<3>"      LOC="3";
NET "DS20"      LOC="133";
NET "DS30"      LOC="68";
NET "DS30ACK<0>"      LOC="79";
NET "DS30ACK<1>"      LOC="78";
NET "DSACK<0>"      LOC="135";
NET "DSACK<1>"      LOC="136";
NET "EXP_BG"      LOC="139";
NET "EXP_BR"      LOC="140";
NET "FC<0>"      LOC="85";
NET "FC<1>"      LOC="82";
NET "FC<2>"      LOC="81";
NET "HALT"      LOC="76";
NET "IDECS<0>"      LOC="58";
NET "IDECS<1>"      LOC="59";
NET "IDEINT"      LOC="57";
NET "IDELED"      LOC="71";
NET "IDEWAIT"      LOC="56";
NET "INT2"      LOC="143";
NET "IOR"      LOC="54";
NET "IOW"      LOC="53";
NET "PUNT"      LOC="142";
NET "RAMCS"      LOC="21";
NET "RAMOE"      LOC="2";
NET "RAMWE"      LOC="17";
NET "RAS"      LOC="20";
NET "RESET"      LOC="40";
NET "RW20"      LOC="134";
NET "RW30"      LOC="64";
NET "RXD"      LOC="34";
NET "RXD_EXT"      LOC="43";
NET "SIZ<0>"      LOC="61";
NET "SIZ<1>"      LOC="69";
NET "STERM"      LOC="77";
NET "TXD"      LOC="33";
NET "TXD_EXT"      LOC="41";

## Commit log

2019-03-28 adding the obv files
2020-04-12 First public version of tf330
2020-04-13 Added JLC PCB Gerbers
2020-04-13 Board images
2020-04-13 Added bom files

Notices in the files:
eagle/tf330.brd:
(C) 2018 S.J Leary
parts and their libraries:
microbuilder: This work is placed in the public domain, and may be freely used for commercial and non-commercial work with the following conditions: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
SparkFun-Retired: Licensing:Creative Commons ShareAlike 4.0 International - https://creativecommons.org/licenses/by-sa/4.0
